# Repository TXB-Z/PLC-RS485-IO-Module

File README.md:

# PLC-RS485-IO-Module
Design and development of a 4DI/4DO PLC I/O expansion module using STM32 and Modbus RTU over RS485.

## 1. Project Overview

This project focuses on the design and development of a digital I/O expansion module for PLC systems using RS485 communication.

The module is designed to provide additional digital input and output channels and communicate with a host device through the Modbus RTU protocol.

### Main Features
- 4 Digital Inputs (DI)
- 4 Digital Outputs (DO)
- STM32 microcontroller-based control system
- RS485 serial communication
- Modbus RTU protocol
- 24V DC power input

## 2. System Architecture

The system consists of the following main functional blocks:

- Power Supply
- STM32 Microcontroller
- Digital Input Interface
- Digital Output Interface
- RS485 Communication Interface

## 3. Hardware Design

### 3.1 Microcontroller
- STM32 microcontroller
- GPIO-based digital I/O control
- UART communication interface

### 3.2 Digital Input
- 4-channel digital input interface
- Optocoupler-based signal isolation
- Designed for 24V industrial signals

### 3.3 Digital Output
- 4-channel relay output
- Transistor driver circuit
- 24V DC relay coils

### 3.4 RS485 Interface
- RS485 transceiver
- Half-duplex communication
- UART-based data transmission

### 3.5 Power Supply
- 24V DC input
- Buck converter for 5V supply
- 3.3V supply for microcontroller

## 4. Firmware Development

The firmware is developed using STM32 HAL.

Main functions:
- Digital input acquisition
- Digital output control
- UART communication
- Modbus RTU data processing

## 5. Communication Testing

The communication interface is tested using:
- USB-to-RS485 converter
- PC-based serial communication software
- Modbus Poll

## 6. Development Status

- Hardware design: In development
- Firmware development: In development
- RS485 communication: Under testing
- Modbus RTU integration: Under testing
- Full system validation: Pending

## 7. Future Improvements

- Complete hardware validation
- Improve communication reliability
- Test with an actual PLC
- Develop additional monitoring functions

## 8. Tools & Technologies

- STM32CubeMX
- Keil MDK
- KiCad / Altium Designer
- Modbus RTU
- RS485
- Modbus Poll

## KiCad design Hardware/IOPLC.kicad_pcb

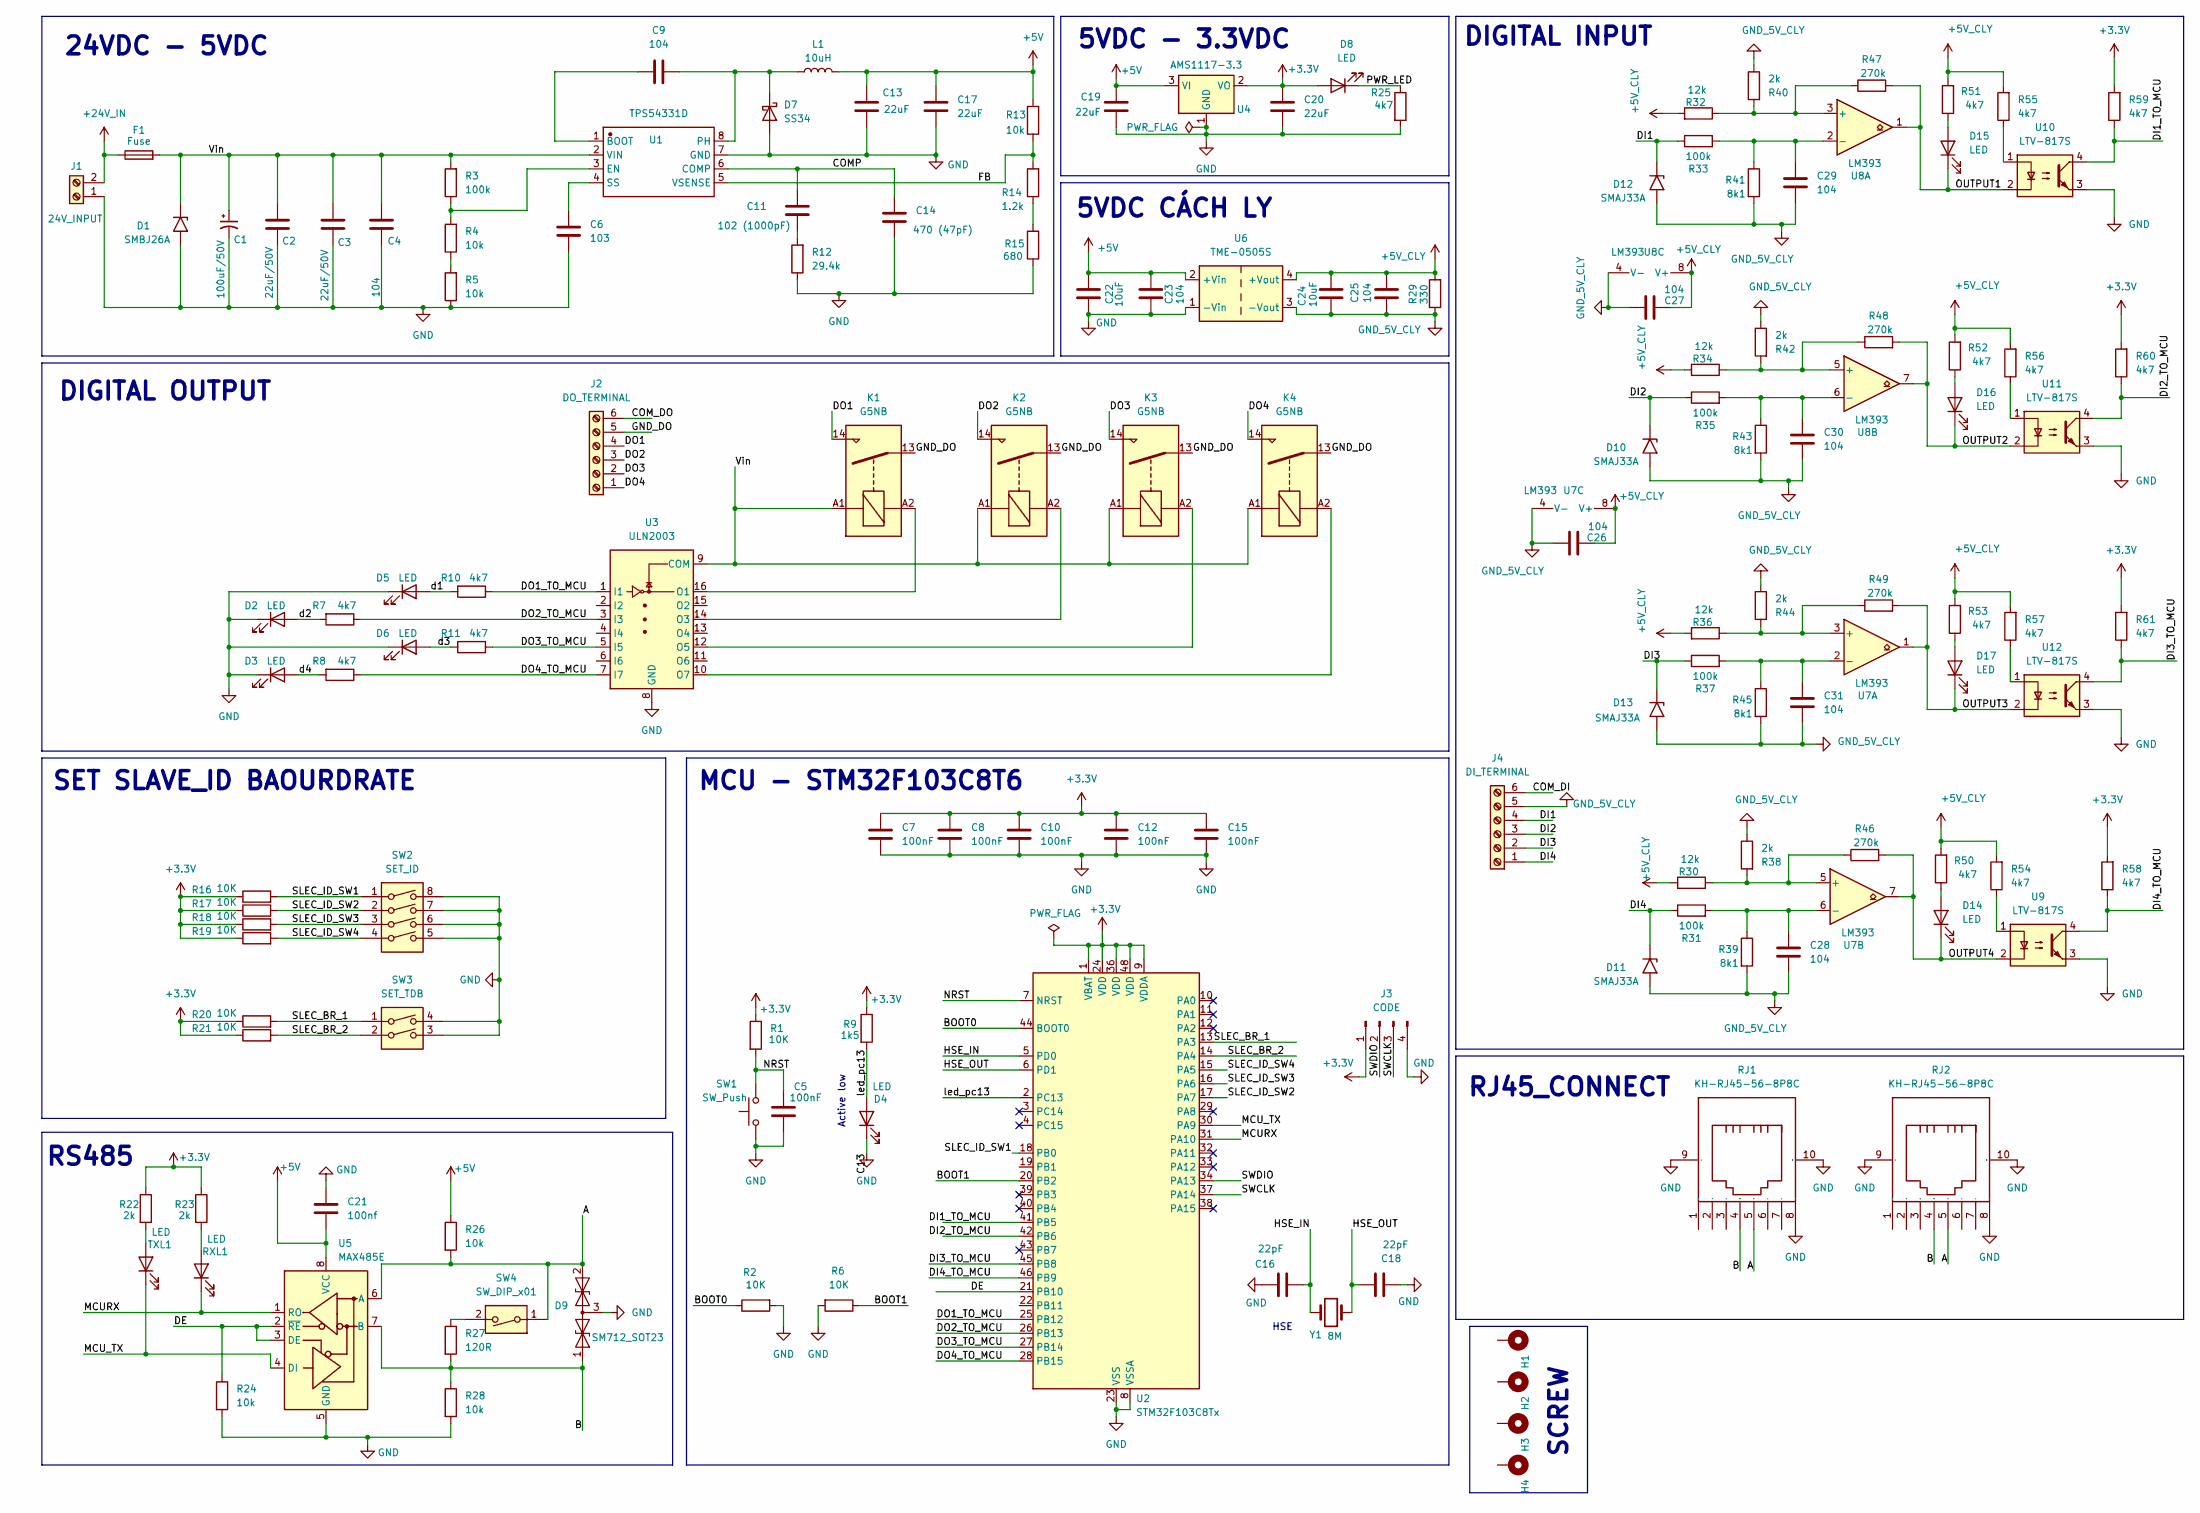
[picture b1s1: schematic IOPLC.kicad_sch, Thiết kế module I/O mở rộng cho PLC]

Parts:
C1: 100uF/50V; CP_Elec_6.3x5.4
C2, C3: 22uF/50V; C_0805_2012Metric_Pad1.18x1.45mm_HandSolder
C4, C9, C23, C25, C26, C27, C28, C29, C30, C31: 104; C_0603_1608Metric_Pad1.08x0.95mm_HandSolder
C5, C7, C8, C10, C12, C15: 100nF; C_0603_1608Metric_Pad1.08x0.95mm_HandSolder
C6: 103; C_0603_1608Metric_Pad1.08x0.95mm_HandSolder
C11: 102 (1000pF); C_0603_1608Metric_Pad1.08x0.95mm_HandSolder
C13, C17, C20: 22uF; C_0805_2012Metric_Pad1.18x1.45mm_HandSolder
C14: 470 (47pF); C_0603_1608Metric_Pad1.08x0.95mm_HandSolder
C16: 22pF; C_0603_1608Metric
C18: 22pF; C_0603_1608Metric_Pad1.08x0.95mm_HandSolder
C19: 22uF; C_0603_1608Metric_Pad1.08x0.95mm_HandSolder
C21: 100nf; C_0603_1608Metric_Pad1.08x0.95mm_HandSolder
C22, C24: 10uF; C_0603_1608Metric_Pad1.08x0.95mm_HandSolder
D1: SMBJ26A; D_SMA
D2, D3, D4, D5, D6, D8, D14, D15, D16, D17: LED; LED_0805_2012Metric_Pad1.15x1.40mm_HandSolder
D7: SS34; D_SMA
D9: SM712_SOT23; SOT-23_Handsoldering
D10, D11, D12, D13: SMAJ33A; D_SMA
F1: Fuse; Fuseholder_Clip-5x20mm_Schurter_CQM_Inline_P20.60x5.00mm_D1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
H1, H2, H3, H4: MountingHole_Pad; MountingHole_2.2mm_M2_Pad_Via
J1: 24V_INPUT; TerminalBlock_MetzConnect_Type073_RT02602HBLU_1x02_P5.08mm_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
J2: DO_TERMINAL; TerminalBlock_Phoenix_MKDS-1,5-6-5.08_1x06_P5.08mm_Horizont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
J3: CODE; PinHeader_1x04_P2.54mm_Vertical
J4: DI_TERMINAL; TerminalBlock_Phoenix_MKDS-1,5-6-5.08_1x06_P5.08mm_Horizont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
K1, K2, K3, K4: G5NB; Relay_SPST_Omron_G5NB
L1: 10uH; L_12x12mm_H6mm
R1, R2, R6, R16, R17, R18, R19, R20, R21: 10K; R_0603_1608Metric_Pad0.98x0.95mm_HandSolder
R3: 100k; R_0603_1608Metric_Pad0.98x0.95mm_HandSolder
R4, R5, R13, R24, R26, R28: 10k; R_0603_1608Metric_Pad0.98x0.95mm_HandSolder
R7, R8, R10, R11, R50, R51, R52, R53, R54, R55, R56, R57, R58, R59, R60, R61: 4k7; R_0603_1608Metric_Pad0.98x0.95mm_HandSolder
R9: 1k5; R_0603_1608Metric_Pad0.98x0.95mm_HandSolder
R12: 29.4k; R_0603_1608Metric_Pad0.98x0.95mm_HandSolder
R14: 1.2k; R_0603_1608Metric_Pad0.98x0.95mm_HandSolder
R15: 680; R_0603_1608Metric_Pad0.98x0.95mm_HandSolder
R22, R23, R38, R40, R42, R44: 2k; R_0603_1608Metric_Pad0.98x0.95mm_HandSolder
R25: 4k7; R_0805_2012Metric_Pad1.20x1.40mm_HandSolder
R27: 120R; R_0603_1608Metric_Pad0.98x0.95mm_HandSolder
R29: 330; R_0603_1608Metric_Pad0.98x0.95mm_HandSolder
R30, R32, R34, R36: 12k; R_0603_1608Metric_Pad0.98x0.95mm_HandSolder
R31, R33, R35, R37: 100k; R_0805_2012Metric_Pad1.20x1.40mm_HandSolder
R39, R41, R43, R45: 8k1; R_0805_2012Metric_Pad1.20x1.40mm_HandSolder
R46, R47, R48, R49: 270k; R_0603_1608Metric_Pad0.98x0.95mm_HandSolder
RJ1, RJ2: KH-RJ45-56-8P8C; RJ45-TH_KH-RJ45-56-8P8C; Manufacturer Part KH-RJ45-56-8P8C
RXL1: LED; LED_0603_1608Metric_Pad1.05x0.95mm_HandSolder
SW1: SW_Push; SW_Tactile_SPST_NO_Straight_CK_PTS636Sx25SMTRLFS
SW2: SET_ID; SW_DIP_SPSTx04_Slide_9.78x12.34mm_W7.62mm_P2.54mm
SW3: SET_TDB; SW_DIP_SPSTx02_Slide_9.78x7.26mm_W7.62mm_P2.54mm
SW4: SW_DIP_x01; SW_DIP_SPSTx01_Slide_9.78x4.72mm_W7.62mm_P2.54mm
TXL1: LED; LED_0603_1608Metric_Pad1.05x0.95mm_HandSolder
U1: TPS54331D; SOIC-8_L4.9-W3.9-P1.27-LS6.0-BL; Manufacturer Part TPS54331D
U2: STM32F103C8Tx; LQFP-48_7x7mm_P0.5mm
U3: ULN2003; SOIC-16_3.9x9.9mm_P1.27mm
U4: AMS1117-3.3; SOT-223-3_TabPin2
U5: MAX485E; SOIC-8_3.9x4.9mm_P1.27mm
U6: TME-0505S; Converter_DCDC_TRACO_TME_03xxS_05xxS_12xxS_Single_THT
U7, U8: LM393; SOIC-8_3.9x4.9mm_P1.27mm
U9, U10, U11, U12: LTV-817S; SMDIP-4_W9.53mm
Y1: 8M; Crystal_SMD_HC49-SD

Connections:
+3.3V: C7.1, C8.1, C10.1, C12.1, C15.1, C20.2, D8.2 (A), J3.1, R1.1, R9.1, R16.1, R17.1, R18.1, R19.1, R20.1, R21.1, R22.1, R23.1, R58.2, R59.2, R60.2, R61.2, U2.1 (VBAT), U2.9 (VDDA), U2.24 (VDD), U2.36 (VDD), U2.48 (VDD), U4.2 (VO)
+5V: C13.1, C17.1, C19.2, C21.2, C22.1, C23.1, L1.2, R13.2, R26.1, U4.3 (VI), U5.8 (VCC), U6.2 (+Vin)
+5V_CLY: C24.2, C25.1, C26.1, C27.1, R29.2, R30.2, R32.2, R34.2, R36.2, R50.2, R51.2, R52.2, R53.2, R54.2, R55.2, R56.2, R57.2, U6.4 (+Vout), U7.8 (V+), U8.8 (V+)
+24V_IN: F1.1, J1.2
/A: D9.2 (A2), R26.2, RJ1.5, RJ2.5, SW4.1, U5.6 (A)
/B: D9.1 (A1), R27.2, R28.1, RJ1.4, RJ2.4, U5.7 (B)
/BOOT0: R2.1, U2.44 (BOOT0)
/BOOT1: R6.1, U2.20 (PB2)
/COMP: C11.1, C14.1, U1.6 (COMP)
/COM_DI: J4.6
/COM_DO: J2.6
/DE: R24.1, U2.21 (PB10), U5.2 (~RE), U5.3 (DE)
/DI1: D12.1 (A1), J4.4, R33.1
/DI1_TO_MCU: R59.1, U2.41 (PB5), U10.4
/DI2: D10.1 (A1), J4.3, R35.1
/DI2_TO_MCU: R60.1, U2.42 (PB6), U11.4
/DI3: D13.1 (A1), J4.2, R37.1
/DI3_TO_MCU: R61.1, U2.45 (PB8), U12.4
/DI4: D11.1 (A1), J4.1, R31.1
/DI4_TO_MCU: R58.1, U2.46 (PB9), U9.4
/DO1: J2.4, K1.14
/DO1_TO_MCU: R10.1, U2.25 (PB12), U3.1 (I1)
/DO2: J2.3, K2.14
/DO2_TO_MCU: R7.1, U2.26 (PB13), U3.3 (I3)
/DO3: J2.2, K3.14
/DO3_TO_MCU: R11.1, U2.27 (PB14), U3.5 (I5)
/DO4: J2.1, K4.14
/DO4_TO_MCU: R8.1, U2.28 (PB15), U3.7 (I7)
/FB: R13.1, R14.2, U1.5 (VSENSE)
/GND_DO: J2.5, K1.13, K2.13, K3.13, K4.13
/HSE_IN: C16.1, U2.5 (PD0), Y1.2
/HSE_OUT: C18.2, U2.6 (PD1), Y1.1
/MCURX: RXL1.1 (K), U2.31 (PA10), U5.1 (RO)
/MCU_TX: TXL1.1 (K), U2.30 (PA9), U5.4 (DI)
/NRST: C5.2, R1.2, SW1.2, U2.7 (NRST)
/OUTPUT1: D15.1 (K), R47.2, U8.1, U10.2
/OUTPUT2: D16.1 (K), R48.2, U8.7, U11.2
/OUTPUT3: D17.1 (K), R49.2, U7.1, U12.2
/OUTPUT4: D14.1 (K), R46.2, U7.7, U9.2
/PWR_LED: D8.1 (K), R25.1
/SLEC_BR_1: R20.2, SW3.1, U2.13 (PA3)
/SLEC_BR_2: R21.2, SW3.2, U2.14 (PA4)
/SLEC_ID_SW1: R16.2, SW2.1, U2.18 (PB0); also elsewhere on the board
/SLEC_ID_SW2: R17.2, SW2.2, U2.17 (PA7); also elsewhere on the board
/SLEC_ID_SW3: R18.2, SW2.3, U2.16 (PA6); also elsewhere on the board
/SLEC_ID_SW4: R19.2, SW2.4, U2.15 (PA5); also elsewhere on the board
/SWCLK: J3.3, U2.37 (PA14)
/SWDIO: J3.2, U2.34 (PA13)
/Vin: C1.1, C2.1, C3.1, C4.1, D1.1 (A1), F1.2, K1.A1, K2.A1, K3.A1, K4.A1, R3.2, U1.2 (VIN), U3.9 (COM)
/d1: D5.2 (A), R10.2
/d2: D2.2 (A), R7.2
/d3: D6.2 (A), R11.2
/d4: D3.2 (A), R8.2
/led_pc13: D4.2 (A), R9.2, U2.2 (PC13)
GND: C1.2, C2.2, C3.2, C4.2, C5.1, C6.2, C7.2, C8.2, C10.2, C12.2, C13.2, C14.2, C15.2, C16.2, C17.2, C18.1, C19.1, C20.1, C21.1, C22.2, C23.2, D1.2 (A2), D2.1 (K), D3.1 (K), D4.1 (K), D5.1 (K), D6.1 (K), D7.2 (A), D9.3 (common), J1.1, J3.4, R2.2, R5.1, R6.2, R12.1, R15.1, R24.2, R25.2, R28.2, RJ1.8, RJ1.9, RJ1.10, RJ2.8, RJ2.9, RJ2.10, SW1.1, SW2.5, SW2.6, SW2.7, SW2.8, SW3.3, SW3.4, U1.7 (GND), U2.8 (VSSA), U2.23 (VSS), U2.35 (VSS), U2.47 (VSS), U3.8 (GND), U4.1 (GND), U5.5 (GND), U6.1 (-Vin), U9.3, U10.3, U11.3, U12.3; also elsewhere on the board
GND_5V_CLY: C24.1, C25.2, C26.2, C27.2, C28.2, C29.2, C30.2, C31.2, D10.2 (A2), D11.2 (A2), D12.2 (A2), D13.2 (A2), J4.5, R29.1, R38.1, R39.2, R40.1, R41.2, R42.1, R43.2, R44.1, R45.2, U6.3 (-Vout), U7.4 (V-), U8.4 (V-)
unnamed: C11.2, R12.2
unnamed: C9.1, D7.1 (K), L1.1, U1.8 (PH)
unnamed: D14.2 (A), R50.1
unnamed: D15.2 (A), R51.1
unnamed: D16.2 (A), R52.1
unnamed: D17.2 (A), R53.1
unnamed: R4.1, R5.2
unnamed: R14.1, R15.2
unnamed: R27.1, SW4.2
unnamed: R54.1, U9.1
unnamed: R55.1, U10.1
unnamed: R56.1, U11.1
unnamed: R57.1, U12.1
unnamed: R23.2, RXL1.2 (A)
unnamed: R22.2, TXL1.2 (A)
unnamed: C9.2, U1.1 (BOOT)
unnamed: R3.1, R4.2, U1.3 (EN)
unnamed: C6.1, U1.4 (SS)
unnamed: K1.A2, U3.16 (O1)
unnamed: K2.A2, U3.14 (O3)
unnamed: K3.A2, U3.12 (O5)
unnamed: K4.A2, U3.10 (O7)
unnamed: R36.1, R44.2, R49.1, U7.3 (+)
unnamed: C31.1, R37.2, R45.1, U7.2 (-)
unnamed: R30.1, R38.2, R46.1, U7.5 (+)
unnamed: C28.1, R31.2, R39.1, U7.6 (-)
unnamed: R32.1, R40.2, R47.1, U8.3 (+)
unnamed: C29.1, R33.2, R41.1, U8.2 (-)
unnamed: R34.1, R42.2, R48.1, U8.5 (+)
unnamed: C30.1, R35.2, R43.1, U8.6 (-)

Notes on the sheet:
Active low
SCREW
5VDC CÁCH LY
DIGITAL OUTPUT
RS485
DIGITAL INPUT
MCU - STM32F103C8T6
HSE
SET SLAVE_ID BAOURDRATE
5VDC - 3.3VDC
RJ45_CONNECT
24VDC - 5VDC

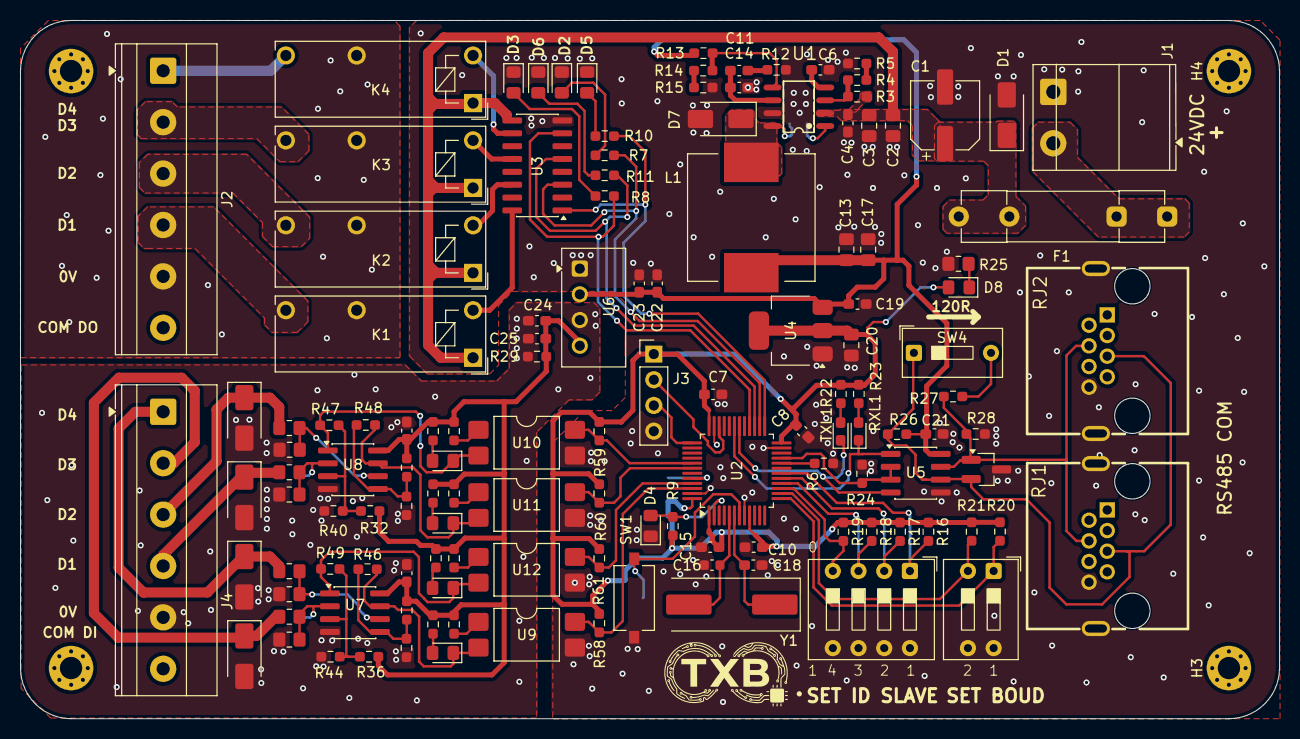
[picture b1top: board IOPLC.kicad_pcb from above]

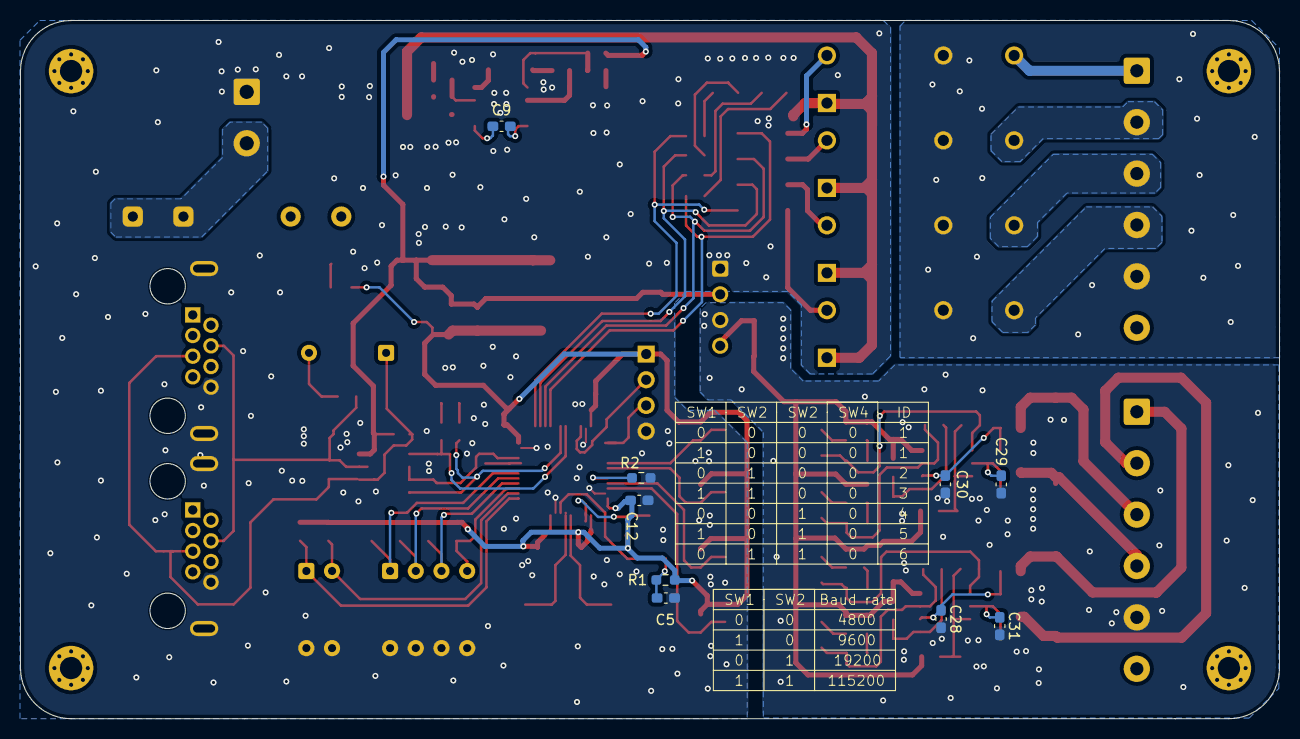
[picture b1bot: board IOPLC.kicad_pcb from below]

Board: 2 copper layers, 124.4 x 69.0 mm, 144 parts (9 on the bottom side), 84 nets.

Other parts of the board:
SET ID SLAVE: SET_ID; SW_DIP_SPSTx04_Slide_9.78x12.34mm_W7.62mm_P2.54mm

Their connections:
/SLEC_ID_SW1: SET ID SLAVE.1; also elsewhere on the board
/SLEC_ID_SW2: SET ID SLAVE.2; also elsewhere on the board
/SLEC_ID_SW3: SET ID SLAVE.3; also elsewhere on the board
/SLEC_ID_SW4: SET ID SLAVE.4; also elsewhere on the board
GND: SET ID SLAVE.5, SET ID SLAVE.6, SET ID SLAVE.7, SET ID SLAVE.8; also elsewhere on the board

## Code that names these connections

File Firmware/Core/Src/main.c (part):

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	HAL_GPIO_Init(GPIOA, &GPIO_InitStruct);
	HAL_GPIO_Init(GPIOA, &GPIO_InitStruct);
	
	/* OUTPUT: PA3 = DE/RE cua MAX485 (mac dinh muc thap = che do nhan) */
GPIO_InitStruct.Pin   = GPIO_PIN_3;
GPIO_InitStruct.Mode  = GPIO_MODE_OUTPUT_PP;
GPIO_InitStruct.Pull  = GPIO_NOPULL;
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	
  __HAL_RCC_GPIOC_CLK_ENABLE();

  /* Configure PC13 as output */
  GPIO_InitStruct.Pin = GPIO_PIN_13;
  GPIO_InitStruct.Mode = GPIO_MODE_OUTPUT_PP;
  GPIO_InitStruct.Speed = GPIO_SPEED_FREQ_LOW;
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	__HAL_RCC_GPIOB_CLK_ENABLE();


/* Configure PB12..PB15 as DO (output push-pull) */
GPIO_InitStruct.Pin   = GPIO_PIN_12 | GPIO_PIN_13 | GPIO_PIN_14 | GPIO_PIN_15| GPIO_PIN_10;
GPIO_InitStruct.Mode  = GPIO_MODE_OUTPUT_PP;
GPIO_InitStruct.Pull  = GPIO_NOPULL;
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HAL_GPIO_Init(GPIOB, &GPIO_InitStruct);
HAL_GPIO_WritePin(GPIOB, GPIO_PIN_12 | GPIO_PIN_13 | GPIO_PIN_14 | GPIO_PIN_15| GPIO_PIN_10, GPIO_PIN_RESET);

/* ===== INPUT: PB0, PB1 (DIP switch) ===== */
GPIO_InitStruct.Pin  = GPIO_PIN_0 | GPIO_PIN_1 | GPIO_PIN_5 | GPIO_PIN_6 | GPIO_PIN_8 | GPIO_PIN_9;
GPIO_InitStruct.Mode = GPIO_MODE_INPUT;      // <-- INPUT
GPIO_InitStruct.Pull = GPIO_PULLUP;
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 *
 *   Cong tac | Chan STM32 | Bit    | Trong so
 *   ---------+------------+--------+---------
 *   SW1      | PB0        | bit 0  | 1   (LSB)
 *   SW2      | PA7        | bit 1  | 2
 *   SW3      | PA6        | bit 2  | 4
 *   SW4      | PA5        | bit 3  | 8   (MSB)
 *
 * Cach dau: moi cong tac noi giua chan STM32 va GND.
 *   - Cong tac ON  (dong) -> chan ve GND -> doc ra muc THAP -> bit = 1
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 *   ...             | ...
 *   ON  ON  ON  ON  | 15
 *
 * Luu y: cac chan nay khong trung voi DI (PA0, PA1, PA4, PA5), DO (PB12..PB15),
 * UART (PA9, PA10), DE/RE (PB6), SWD (PA13, PA14).
 * =====================================================================================
 */
     uint8_t id = 0;
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    }
}

// bd 1 PA3
//BD 2 PA4
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
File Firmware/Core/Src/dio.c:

#include "dio.h"
#include "rs485.h"
//* chon toc do giaot iep////////////////////////////////////////////////
uint32_t baud_rate = 4800;
uint32_t t35_ms    = 5;

void Baud_Init(void)
{
    static const uint32_t baud_table[4] = {4800, 9600, 19200, 115200};
    uint8_t sel = 0;

    if (HAL_GPIO_ReadPin(GPIOA, GPIO_PIN_3) == GPIO_PIN_RESET) sel |= 0x01;   // SW1
    if (HAL_GPIO_ReadPin(GPIOA, GPIO_PIN_4) == GPIO_PIN_RESET) sel |= 0x02;   // SW2

    baud_rate = baud_table[sel];

    // T3.5 = 3.5 ky tu x 11 bit / baud, lam tron len; tren 19200 chuan co dinh 1.75 ms
    if (baud_rate > 19200) t35_ms = 2;
    else                   t35_ms = (38500UL / baud_rate) + 1;
}

/*
 * Phan cong chan dau vao so (DI):
 *
 * PB5 -> DI1
 * PB6 -> DI2
 * PB8 -> DI3
 * PB9 -> DI4
 *
 * Cac chan duoc lua chon nham dam bao 4 kenh DI hoat dong doc lap,
 * khong xung dot voi cac ngoai vi chinh cua he thong nhu USART1
 * dung cho truyen thong RS485, cac chan dieu khien DO, DE/RE,
 * cau hinh dia chi thiet bi va giao tiep SWD.
 */
 
 /*
 * Phan cong chan dau ra so (DO):
 *
 * PB12 -> DO1
 * PB13 -> DO2
 * PB14 -> DO3
 * PB15 -> DO4
 *
 * Cac chan duoc lua chon nham dam bao 4 kenh Do hoat dong doc lap,
 * khong xung dot voi cac ngoai vi chinh cua he thong nhu USART1
 * dung cho truyen thong RS485, cac chan dieu khien DO, DE/RE,
 * cau hinh dia chi thiet bi va giao tiep SWD.
 */
 
/*******************************************************************************************************************/	
/*******************************************************************************************************************/			
/*******************************************************************************************************************/			
/*******************************************************************************************************************/			
																			/***** mã code FC02********/
	// hàm doc 1 di rieng le
uint8_t Read_sigle_di(uint16_t address)
	{
			switch (address)
			{
					case 0:
							return HAL_GPIO_ReadPin(GPIOB, GPIO_PIN_5);
					case 1:
							return HAL_GPIO_ReadPin(GPIOB, GPIO_PIN_6);
					case 2:
							return HAL_GPIO_ReadPin(GPIOB, GPIO_PIN_8);
					case 3:
							return HAL_GPIO_ReadPin(GPIOB, GPIO_PIN_9);
					default:
							return 0;
			}
	}
	
	// doc di theo vi tri tu frame
uint8_t DI_ReadRange(uint16_t start_address, uint16_t quantity)
	{
			uint8_t data = 0;
			for (uint16_t i = 0; i < quantity; i++)
			{
					if (Read_sigle_di(start_address + i))
					{
							data |= (1 << i);
					}
			}
			return data;
	}
	
uint8_t Handle_Read_Data_DI(uint8_t *frame, uint16_t size)// ham xu ly doc ra trang thai các di
	{
		uint16_t address;
    uint16_t quantity;
    uint8_t data;

    address = ((uint16_t)frame[2] << 8) | frame[3];
    quantity = ((uint16_t)frame[4] << 8) | frame[5];
		return DI_ReadRange(address,quantity);
	}

	
void Handle_Read_DI(uint8_t *rx_buffer, uint16_t rx_size)// tao data repons va gui len
	{
		uint8_t  di_data = Handle_Read_Data_DI(rx_buffer, rx_size);
		uint8_t  tx_buf[8];
		uint16_t tx_len  = Build_Response_FC02(tx_buf, rx_buffer[0], di_data);
		RS485_Send(tx_buf, tx_len);
	}

/*******************************************************************************************************************/	
/*******************************************************************************************************************/			
/*******************************************************************************************************************/			
/*******************************************************************************************************************/			
																			/***** mã code FC01********/
	uint8_t Read_sigle_do(uint16_t address)// doc tung do
	{
			switch (address)
			{
					case 0:
							return HAL_GPIO_ReadPin(GPIOB, GPIO_PIN_12);
					case 1:
							return HAL_GPIO_ReadPin(GPIOB, GPIO_PIN_13);
					case 2:
							return HAL_GPIO_ReadPin(GPIOB, GPIO_PIN_14);
					case 3:
							return HAL_GPIO_ReadPin(GPIOB, GPIO_PIN_15);
					default:
							return 0;
			}
	}
	
uint8_t DO_ReadRange(uint16_t start_address, uint16_t quantity)// gom toan bo data do
	{
			uint8_t data = 0;
			for (uint16_t i = 0; i < quantity; i++)
			{
					if (Read_sigle_do(start_address + i))
					{
							data |= (1 << i);
					}
			}
			return data;
	}
	
	uint8_t Handle_Read_Data_DO(uint8_t *frame, uint16_t size)// ham xu ly doc ra trang thai các di
	{
		uint16_t address;
    uint16_t quantity;
    uint8_t data;

    address = ((uint16_t)frame[2] << 8) | frame[3];
    quantity = ((uint16_t)frame[4] << 8) | frame[5];
		return DO_ReadRange(address,quantity);
	}
	
void Handle_Read_DO(uint8_t *rx_buffer, uint16_t rx_size)// tao data repons va gui len
	{
		uint8_t  do_data = Handle_Read_Data_DO(rx_buffer, rx_size);
		uint8_t  tx_buf[8];
		uint16_t tx_len  = Build_Response_FC01(tx_buf, rx_buffer[0], do_data);
		RS485_Send(tx_buf, tx_len);
	}
/*******************************************************************************************************************/	
/*******************************************************************************************************************/			
/*******************************************************************************************************************/			
/*******************************************************************************************************************/			
																			/***** mã code FC05********/
																					/* dk le DO*/
	void Handle_Write_SINGLE_DO(uint8_t *frame, uint16_t size)// ham xu ly dieu khien 1 di
	{
		//if (size != 8) return;
		uint16_t address;
    uint16_t state_of_DO;//

    address = ((uint16_t)frame[2] << 8) | frame[3];
    state_of_DO = ((uint16_t)frame[4] << 8) | frame[5];
		
			switch (address)
				{
				case 0x00:
						if(state_of_DO == 0xff00) HAL_GPIO_WritePin(GPIOB,GPIO_PIN_12,1);
						else if (state_of_DO == 0x0000) HAL_GPIO_WritePin(GPIOB,GPIO_PIN_12,0);
						break;
				case 0x01:
						if(state_of_DO == 0xff00) HAL_GPIO_WritePin(GPIOB,GPIO_PIN_13,1);
						else if (state_of_DO == 0x0000) HAL_GPIO_WritePin(GPIOB,GPIO_PIN_13,0);
						break;
				case 0x02:
						if(state_of_DO == 0xff00) HAL_GPIO_WritePin(GPIOB,GPIO_PIN_14,1);
						else if (state_of_DO == 0x0000) HAL_GPIO_WritePin(GPIOB,GPIO_PIN_14,0);
						break;
				case 0x03:
						if(state_of_DO == 0xff00) HAL_GPIO_WritePin(GPIOB,GPIO_PIN_15,1);
						else if (state_of_DO == 0x0000) HAL_GPIO_WritePin(GPIOB,GPIO_PIN_15,0);
						break;
				}
			RS485_Send(frame,size);
		
	}
	
/*******************************************************************************************************************/	
/*******************************************************************************************************************/			
/*******************************************************************************************************************/			
/*******************************************************************************************************************/			
																			/***** mã code FC0F********/
																					/* dk nhieu DO*/
	void Handle_Write_Multiple_DO(uint8_t *frame, uint16_t size)// ham xu ly dieu khien nhieu di
	{   
		uint16_t address;
    uint16_t quantity;
		uint8_t byte_count;
		uint8_t data;
		address = ((uint16_t)frame[2] << 8) | frame[3];
    quantity = ((uint16_t)frame[4] << 8) | frame[5];
		byte_count = frame[6];
		data = frame[7];
		if(address >= 4)return;
		if(quantity == 0) return;
		if((address + quantity) > 4) return;
		Write_Multiple_DO(address,quantity,data);
		uint8_t  tx_buf[8];
		uint16_t tx_len  = Build_Response_FC0f(tx_buf, address ,quantity,frame[0]);
		RS485_Send(tx_buf, tx_len);
	}
void Write_Multiple_DO(uint16_t address, uint16_t quantity, uint8_t data)
{
    for (uint16_t i = 0; i < quantity; i++)
    {
        uint8_t state = (data >> i) & 0x01;   // bit th? i c?a data
        Write_Single(address + i, state);     // chân th? address + i
    }
}

void Write_Single(uint16_t address, uint8_t state)
{
    GPIO_PinState pin_state;

    pin_state = state ? GPIO_PIN_SET : GPIO_PIN_RESET;

    switch (address)
    {
        case 0:
            HAL_GPIO_WritePin(GPIOB, GPIO_PIN_12, pin_state);
            break;

        case 1:
            HAL_GPIO_WritePin(GPIOB, GPIO_PIN_13, pin_state);
            break;

        case 2:
            HAL_GPIO_WritePin(GPIOB, GPIO_PIN_14, pin_state);
            break;

        case 3:
            HAL_GPIO_WritePin(GPIOB, GPIO_PIN_15, pin_state);
            break;
    }
}
